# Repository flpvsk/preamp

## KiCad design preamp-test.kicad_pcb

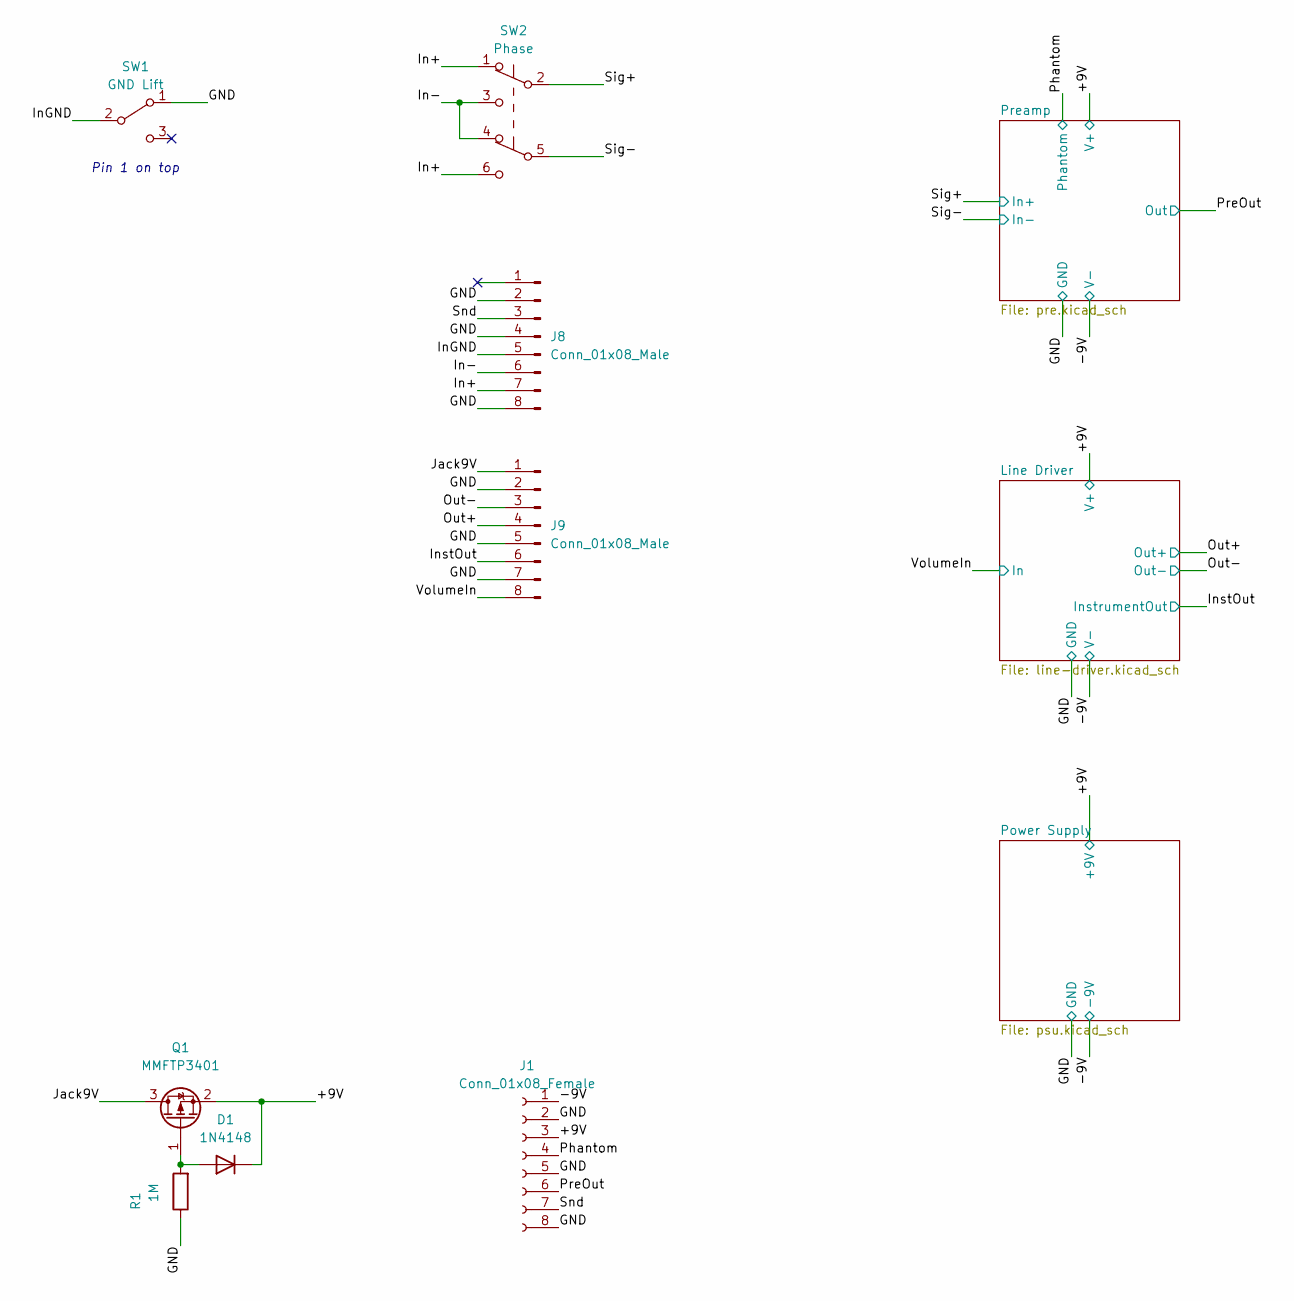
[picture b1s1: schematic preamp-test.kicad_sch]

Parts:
D1: 1N4148; D_SOD-323_HandSoldering
J1: Conn_01x08_Female; PinSocket_1x08_P2.54mm_Vertical
J8, J9: Conn_01x08_Male; Molex_Picoflex_90814-0008_2x04_P1.27mm_Vertical
Q1: MMFTP3401; SOT-23
R1: 1M; R_0603_1608Metric_Pad0.98x0.95mm_HandSolder
SW1: GND Lift; SPDT.LUGS
SW2: Phase; DPDT.LUGS

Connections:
/+9V: D1.1 (K), J1.3, Q1.2 (S); also elsewhere on the board
/-9V: J1.1; also elsewhere on the board
/GND: J1.2, J1.5, J1.8, J8.2, J8.4, J8.8, J9.2, J9.5, J9.7, R1.1, SW1.1 (A); also elsewhere on the board
/In+: J8.7, SW2.1 (A), SW2.6 (C)
/In-: J8.6, SW2.3 (C), SW2.4 (A)
/InGND: J8.5, SW1.2 (B)
/InstOut: J9.6; also elsewhere on the board
/Jack9V: J9.1, Q1.3 (D)
/Out+: J9.4; also elsewhere on the board
/Out-: J9.3; also elsewhere on the board
/Phantom: J1.4; also elsewhere on the board
/PreOut: J1.6; also elsewhere on the board
/Sig+: SW2.2 (B); also elsewhere on the board
/Sig-: SW2.5 (B); also elsewhere on the board
/Snd: J1.7, J8.3
/VolumeIn: J9.8; also elsewhere on the board
unnamed: D1.2 (A), Q1.1 (G), R1.2

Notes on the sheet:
Pin 1 on top

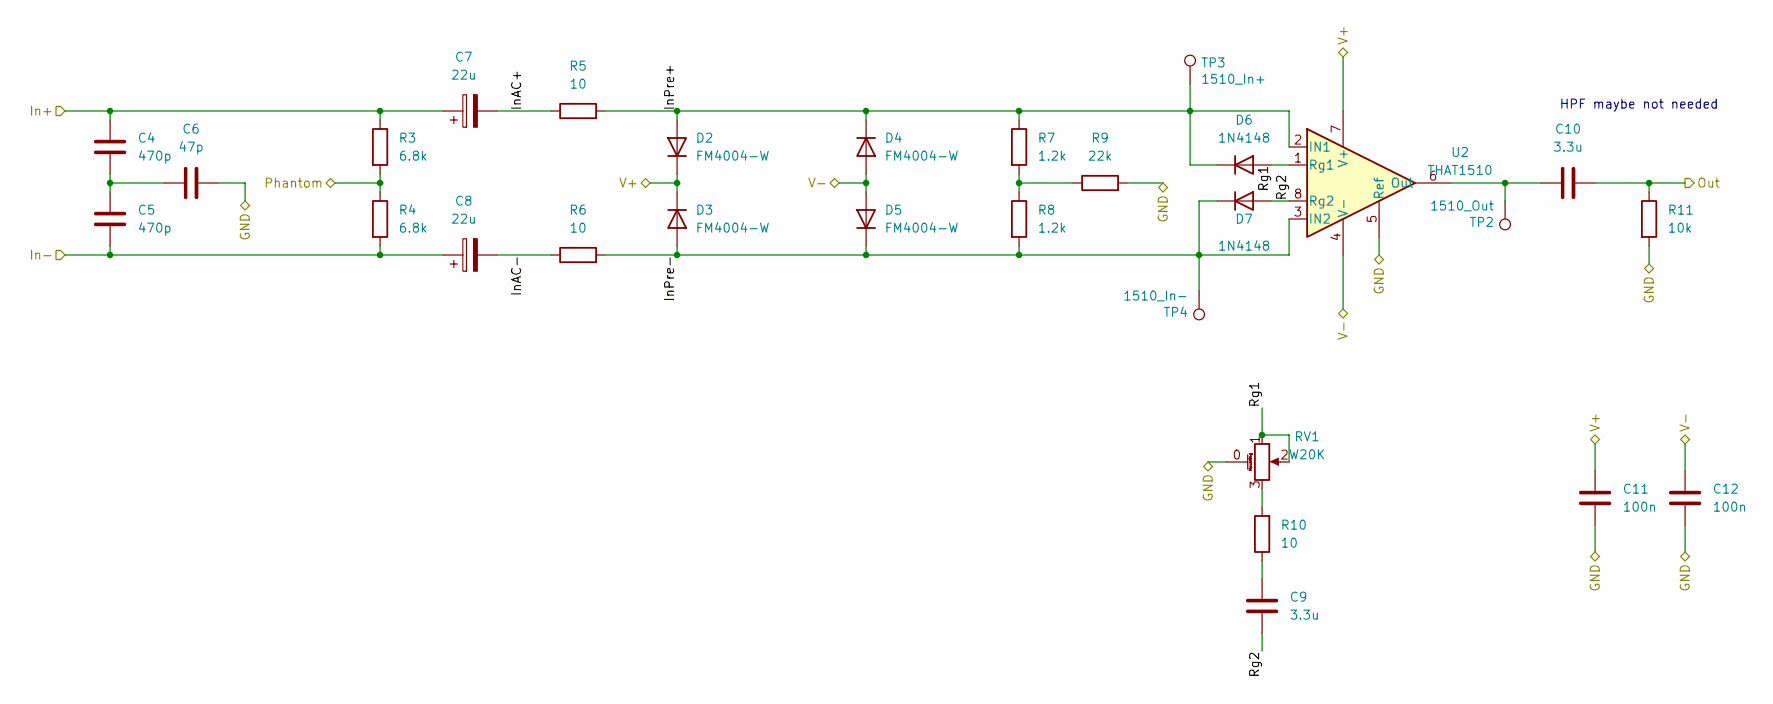
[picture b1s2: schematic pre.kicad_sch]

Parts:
C4, C5: 470p; C_0603_1608Metric_Pad1.08x0.95mm_HandSolder
C6: 47p; C_0603_1608Metric_Pad1.08x0.95mm_HandSolder
C7, C8: 22u; CP_Elec_6.3x5.8
C9, C10: 3.3u; C_1206_3216Metric_Pad1.33x1.80mm_HandSolder
C11, C12: 100n; C_0603_1608Metric_Pad1.08x0.95mm_HandSolder
D2, D3, D4, D5: FM4004-W; D_SMA_Handsoldering
D6, D7: 1N4148; D_SOD-323_HandSoldering
R3, R4: 6.8k; R_0603_1608Metric_Pad0.98x0.95mm_HandSolder
R5, R6, R10: 10; R_0603_1608Metric_Pad0.98x0.95mm_HandSolder
R7, R8: 1.2k; R_0603_1608Metric_Pad0.98x0.95mm_HandSolder
R9: 22k; R_0603_1608Metric_Pad0.98x0.95mm_HandSolder
R11: 10k; R_0603_1608Metric_Pad0.98x0.95mm_HandSolder
RV1: W20K; V3_TRIM_R0904NB10KL-Keepout
TP2: 1510_Out; TestPoint_THTPad_D1.5mm_Drill0.7mm
TP3: 1510_In+; TestPoint_THTPad_D1.5mm_Drill0.7mm
TP4: 1510_In-; TestPoint_THTPad_D1.5mm_Drill0.7mm
U2: THAT1510; SOIC-8_3.9x4.9mm_P1.27mm

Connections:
/+9V: C11.2, D2.1 (K), D3.1 (K), U2.7 (V+); also elsewhere on the board
/-9V: C12.2, D4.2 (A), D5.2 (A), U2.4 (V-); also elsewhere on the board
/GND: C6.2, C11.1, C12.1, R9.2, R11.2, RV1.0 (ShieldPin), U2.5 (Ref); also elsewhere on the board
/Phantom: R3.2, R4.1; also elsewhere on the board
/PreOut: C10.2, R11.1; also elsewhere on the board
/Preamp/InAC+: C7.2, R5.1
/Preamp/InAC-: C8.2, R6.1
/Preamp/InPre+: D2.2 (A), D4.1 (K), D6.1 (K), R5.2, R7.1, TP3.1, U2.2 (IN1)
/Preamp/InPre-: D3.2 (A), D5.1 (K), D7.1 (K), R6.2, R8.2, TP4.1, U2.3 (IN2)
/Preamp/Rg1: D6.2 (A), RV1.1, RV1.2, U2.1 (Rg1)
/Preamp/Rg2: C9.2, D7.2 (A), U2.8 (Rg2)
/Sig+: C4.1, C7.1, R3.1; also elsewhere on the board
/Sig-: C5.2, C8.1, R4.2; also elsewhere on the board
unnamed: C4.2, C5.1, C6.1
unnamed: C9.1, R10.1
unnamed: C10.1, TP2.1, U2.6 (Out)
unnamed: R7.2, R8.1, R9.1
unnamed: R10.2, RV1.3

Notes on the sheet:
HPF maybe not needed

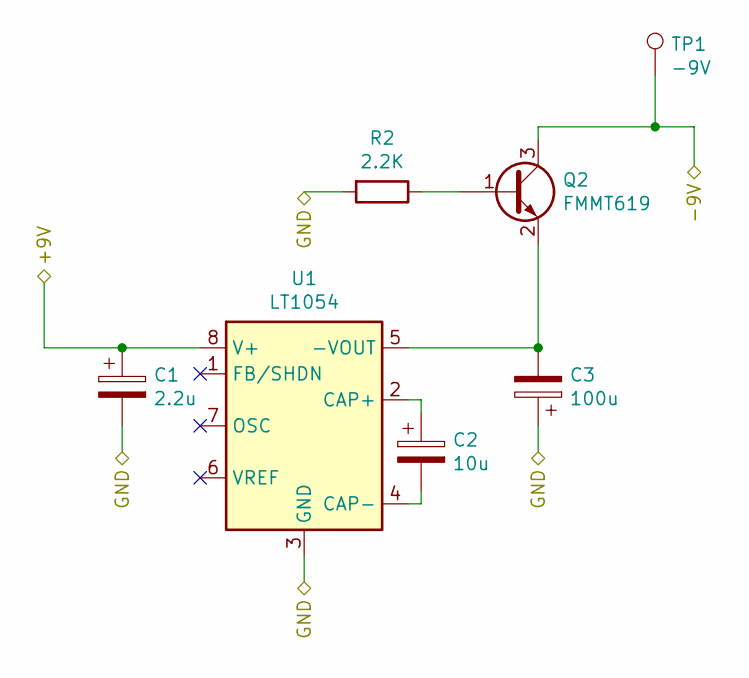
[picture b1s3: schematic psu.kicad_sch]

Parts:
C1: 2.2u; CP_Elec_4x5.4
C2: 10u; CP_EIA-6032-28_Kemet-C_Pad2.25x2.35mm_HandSolder
C3: 100u; CP_EIA-6032-28_Kemet-C_Pad2.25x2.35mm_HandSolder
Q2: FMMT619; SOT-23_Handsoldering
R2: 2.2K; R_0603_1608Metric_Pad0.98x0.95mm_HandSolder
TP1: -9V; TestPoint_THTPad_D1.5mm_Drill0.7mm
U1: LT1054; SOIC-8_3.9x4.9mm_P1.27mm

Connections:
/+9V: C1.1, U1.8 (V+); also elsewhere on the board
/-9V: Q2.3 (C), TP1.1; also elsewhere on the board
/GND: C1.2, C3.1, R2.2, U1.3 (GND); also elsewhere on the board
unnamed: C2.1, U1.2 (CAP+)
unnamed: C2.2, U1.4 (CAP-)
unnamed: C3.2, Q2.2 (E), U1.5 (-VOUT)
unnamed: Q2.1 (B), R2.1

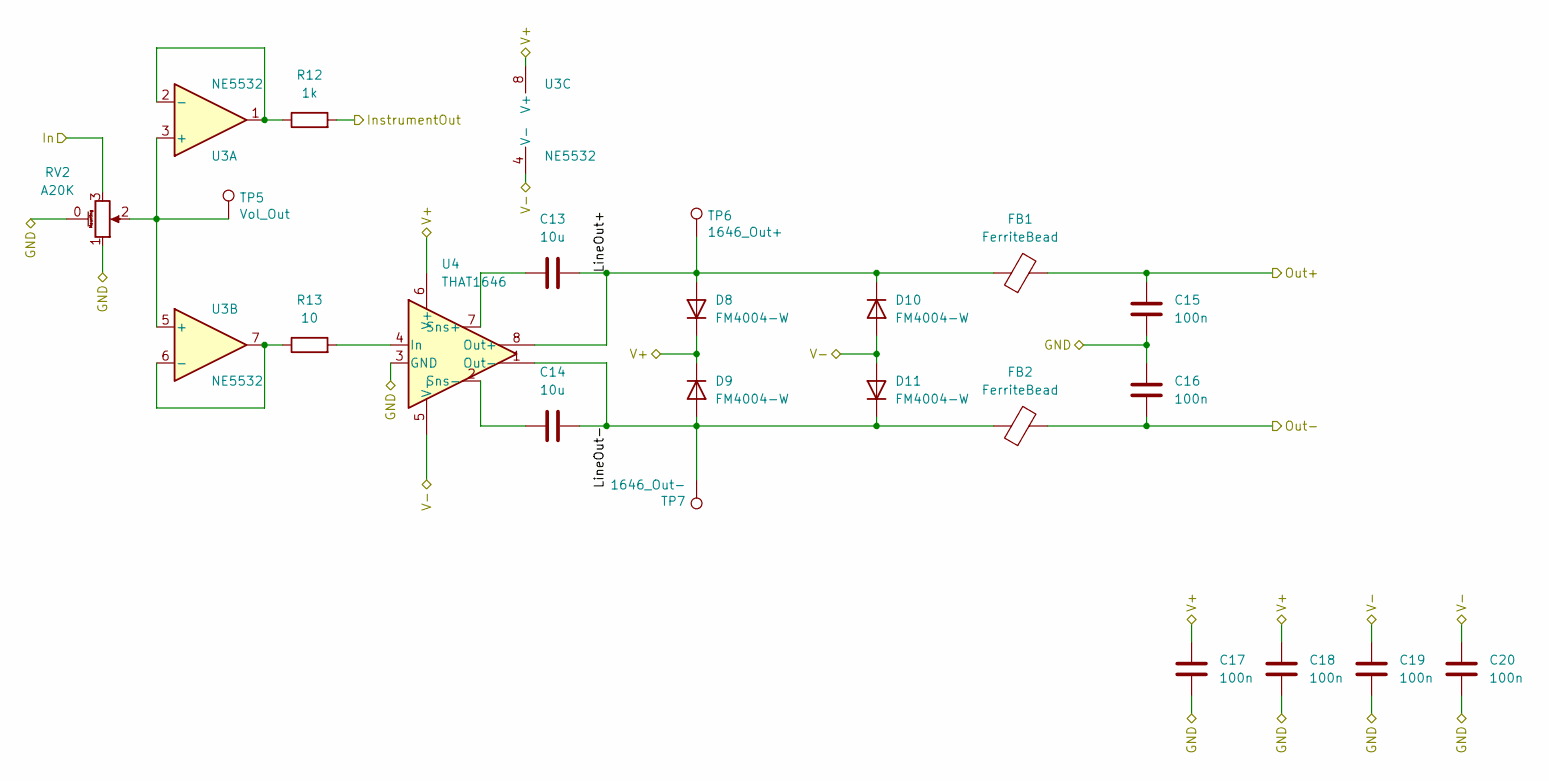
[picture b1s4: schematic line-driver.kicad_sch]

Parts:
C13, C14: 10u; C_1206_3216Metric_Pad1.33x1.80mm_HandSolder
C15, C16, C17, C18, C19, C20: 100n; C_0603_1608Metric_Pad1.08x0.95mm_HandSolder
D8, D9, D10, D11: FM4004-W; D_SMA_Handsoldering
FB1, FB2: FerriteBead; R_0603_1608Metric_Pad0.98x0.95mm_HandSolder
R12: 1k; R_0603_1608Metric_Pad0.98x0.95mm_HandSolder
R13: 10; R_0603_1608Metric_Pad0.98x0.95mm_HandSolder
RV2: A20K; V3_TRIM_R0904NB10KL-Keepout
TP5: Vol_Out; TestPoint_THTPad_D1.5mm_Drill0.7mm
TP6: 1646_Out+; TestPoint_THTPad_D1.5mm_Drill0.7mm
TP7: 1646_Out-; TestPoint_THTPad_D1.5mm_Drill0.7mm
U3: NE5532; SOIC-8_3.9x4.9mm_P1.27mm
U4: THAT1646; SOIC-8_3.9x4.9mm_P1.27mm

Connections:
/+9V: C17.2, C18.2, D8.1 (K), D9.1 (K), U3.8 (V+), U4.6 (V+); also elsewhere on the board
/-9V: C19.2, C20.2, D10.2 (A), D11.2 (A), U3.4 (V-), U4.5 (V-); also elsewhere on the board
/GND: C15.1, C16.2, C17.1, C18.1, C19.1, C20.1, RV2.0 (ShieldPin), RV2.1, U4.3 (GND); also elsewhere on the board
/InstOut: R12.2; also elsewhere on the board
/Line Driver/LineOut+: C13.2, D8.2 (A), D10.1 (K), FB1.1, TP6.1, U4.8 (Out+)
/Line Driver/LineOut-: C14.2, D9.2 (A), D11.1 (K), FB2.1, TP7.1, U4.1 (Out-)
/Out+: C15.2, FB1.2; also elsewhere on the board
/Out-: C16.1, FB2.2; also elsewhere on the board
/VolumeIn: RV2.3; also elsewhere on the board
unnamed: C13.1, U4.7 (Sns+)
unnamed: C14.1, U4.2 (Sns-)
unnamed: R12.1, U3.1, U3.2 (-)
unnamed: R13.1, U3.6 (-), U3.7
unnamed: R13.2, U4.4 (In)
unnamed: RV2.2, TP5.1, U3.3 (+), U3.5 (+)

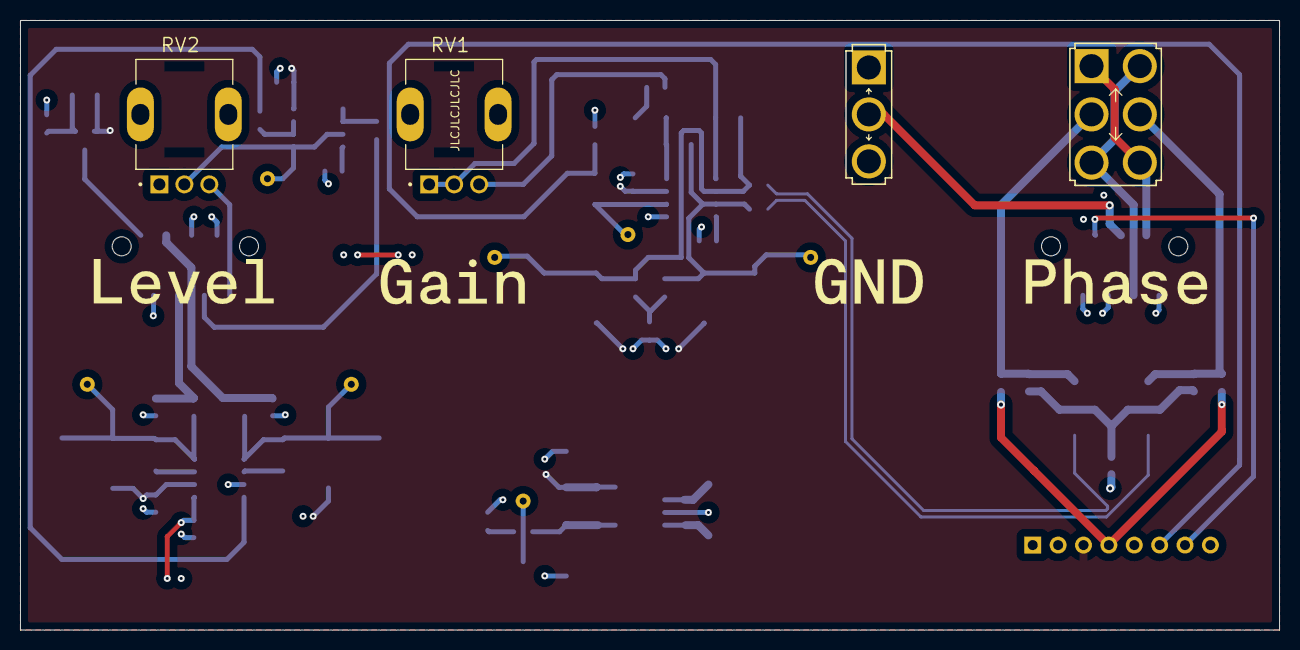
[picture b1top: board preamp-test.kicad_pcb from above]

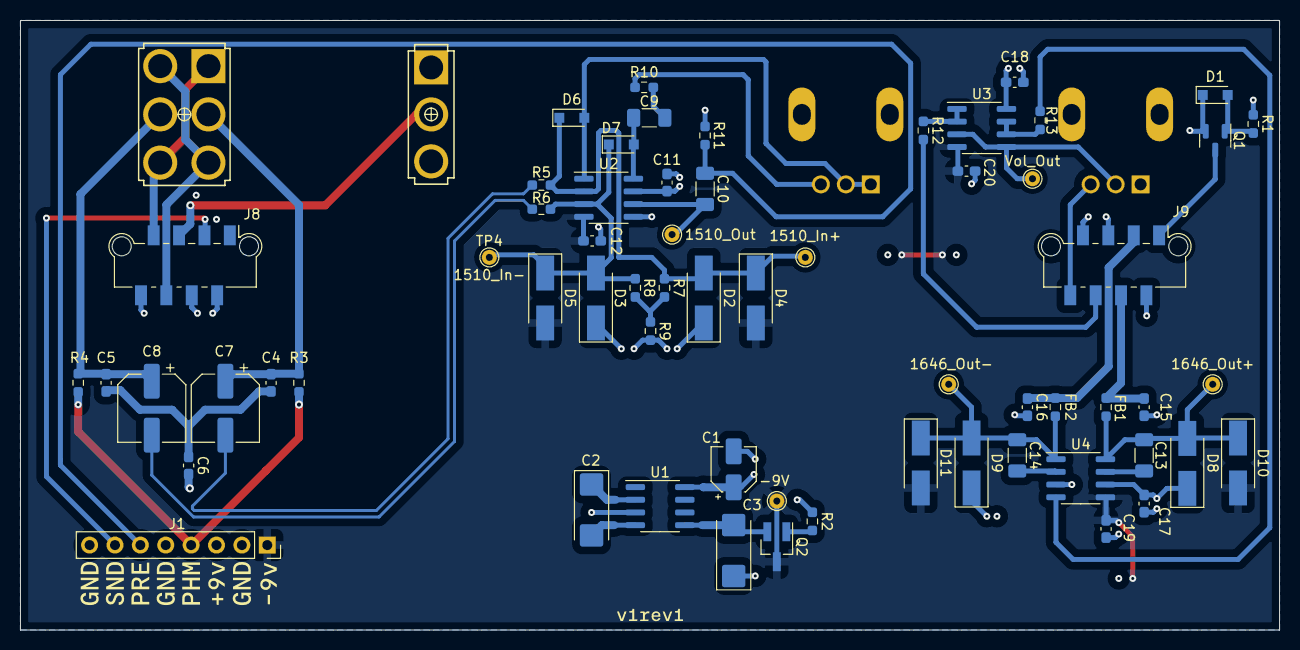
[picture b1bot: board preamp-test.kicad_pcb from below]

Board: 4 copper layers, 126.0 x 61.0 mm, 80 parts (71 on the bottom side), 40 nets.

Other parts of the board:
Ref**: Val**; 1590XX
kibuzzard-66CA6E97: G***; kibuzzard-66CA6E97
kibuzzard-66CA6ECA: G***; kibuzzard-66CA6ECA
kibuzzard-66CA6F29: G***; kibuzzard-66CA6F29
kibuzzard-66CA6F40: G***; kibuzzard-66CA6F40
kibuzzard-66CB7A1F: G***; kibuzzard-66CB7A1F
kibuzzard-66CB7A30, kibuzzard-66CB7A30#2, kibuzzard-66CB7A30#3: G***; kibuzzard-66CB7A30
kibuzzard-66CB7A55: G***; kibuzzard-66CB7A55
kibuzzard-66CB7AA0: G***; kibuzzard-66CB7AA0
kibuzzard-66CB7AA6: G***; kibuzzard-66CB7AA6
kibuzzard-66CB7AAB: G***; kibuzzard-66CB7AAB
kibuzzard-66CB7C93: G***; kibuzzard-66CB7C93

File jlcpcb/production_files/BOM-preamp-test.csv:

Comment,Designator,Footprint,LCSC
Conn_01x08_Female,J1,PinSocket_1x08_P2.54mm_Vertical,
GND Lift,SW1,SPDT.LUGS,
A20K,RV2,V3_TRIM_R0904NB10KL-Keepout,
W20K,RV1,V3_TRIM_R0904NB10KL-Keepout,
Phase,SW2,DPDT.LUGS,
2.2K,R2,R_0603_1608Metric_Pad0.98x0.95mm_HandSolder,
1.2k,R7,R_0603_1608Metric_Pad0.98x0.95mm_HandSolder,
100n,C17,C_0603_1608Metric_Pad1.08x0.95mm_HandSolder,
10,R5,R_0603_1608Metric_Pad0.98x0.95mm_HandSolder,
MMFTP3401,Q1,SOT-23,
Conn_01x08_Male,J8,Molex_Picoflex_90814-0008_2x04_P1.27mm_Vertical,
1N4148,D1,D_SOD-323_HandSoldering,
1510_In+,TP3,TestPoint_THTPad_D1.5mm_Drill0.7mm,
1k,R12,R_0603_1608Metric_Pad0.98x0.95mm_HandSolder,
FM4004-W,D3,D_SMA_Handsoldering,
10,R6,R_0603_1608Metric_Pad0.98x0.95mm_HandSolder,
47p,C6,C_0603_1608Metric_Pad1.08x0.95mm_HandSolder,
22k,R9,R_0603_1608Metric_Pad0.98x0.95mm_HandSolder,
-9V,TP1,TestPoint_THTPad_D1.5mm_Drill0.7mm,
100n,C20,C_0603_1608Metric_Pad1.08x0.95mm_HandSolder,
1510_In-,TP4,TestPoint_THTPad_D1.5mm_Drill0.7mm,
FM4004-W,D10,D_SMA_Handsoldering,
Conn_01x08_Male,J9,Molex_Picoflex_90814-0008_2x04_P1.27mm_Vertical,
THAT1510,U2,SOIC-8_3.9x4.9mm_P1.27mm,
FM4004-W,D5,D_SMA_Handsoldering,
LT1054,U1,SOIC-8_3.9x4.9mm_P1.27mm,
1646_Out-,TP7,TestPoint_THTPad_D1.5mm_Drill0.7mm,
FMMT619,Q2,SOT-23_Handsoldering,
FM4004-W,D8,D_SMA_Handsoldering,
10u,C14,C_1206_3216Metric_Pad1.33x1.80mm_HandSolder,
1N4148,D6,D_SOD-323_HandSoldering,
1510_Out,TP2,TestPoint_THTPad_D1.5mm_Drill0.7mm,
3.3u,C9,C_1206_3216Metric_Pad1.33x1.80mm_HandSolder,
100n,C16,C_0603_1608Metric_Pad1.08x0.95mm_HandSolder,
2.2u,C1,CP_Elec_4x5.4,
1.2k,R8,R_0603_1608Metric_Pad0.98x0.95mm_HandSolder,
10u,C13,C_1206_3216Metric_Pad1.33x1.80mm_HandSolder,
1646_Out+,TP6,TestPoint_THTPad_D1.5mm_Drill0.7mm,
22u,C8,CP_Elec_6.3x5.8,
22u,C7,CP_Elec_6.3x5.8,
100n,C19,C_0603_1608Metric_Pad1.08x0.95mm_HandSolder,
10u,C2,CP_EIA-6032-28_Kemet-C_Pad2.25x2.35mm_HandSolder,
FM4004-W,D9,D_SMA_Handsoldering,
FerriteBead,FB2,R_0603_1608Metric_Pad0.98x0.95mm_HandSolder,
6.8k,R4,R_0603_1608Metric_Pad0.98x0.95mm_HandSolder,
100n,C12,C_0603_1608Metric_Pad1.08x0.95mm_HandSolder,
FM4004-W,D2,D_SMA_Handsoldering,
100n,C11,C_0603_1608Metric_Pad1.08x0.95mm_HandSolder,
10,R10,R_0603_1608Metric_Pad0.98x0.95mm_HandSolder,
100n,C15,C_0603_1608Metric_Pad1.08x0.95mm_HandSolder,
470p,C4,C_0603_1608Metric_Pad1.08x0.95mm_HandSolder,
10k,R11,R_0603_1608Metric_Pad0.98x0.95mm_HandSolder,
THAT1646,U4,SOIC-8_3.9x4.9mm_P1.27mm,
100n,C18,C_0603_1608Metric_Pad1.08x0.95mm_HandSolder,
1N4148,D7,D_SOD-323_HandSoldering,
6.8k,R3,R_0603_1608Metric_Pad0.98x0.95mm_HandSolder,
NE5532,U3,SOIC-8_3.9x4.9mm_P1.27mm,
10,R13,R_0603_1608Metric_Pad0.98x0.95mm_HandSolder,
FerriteBead,FB1,R_0603_1608Metric_Pad0.98x0.95mm_HandSolder,
FM4004-W,D4,D_SMA_Handsoldering,
Vol_Out,TP5,TestPoint_THTPad_D1.5mm_Drill0.7mm,
100u,C3,CP_EIA-6032-28_Kemet-C_Pad2.25x2.35mm_HandSolder,
FM4004-W,D11,D_SMA_Handsoldering,
470p,C5,C_0603_1608Metric_Pad1.08x0.95mm_HandSolder,
1M,R1,R_0603_1608Metric_Pad0.98x0.95mm_HandSolder,
3.3u,C10,C_1206_3216Metric_Pad1.33x1.80mm_HandSolder,

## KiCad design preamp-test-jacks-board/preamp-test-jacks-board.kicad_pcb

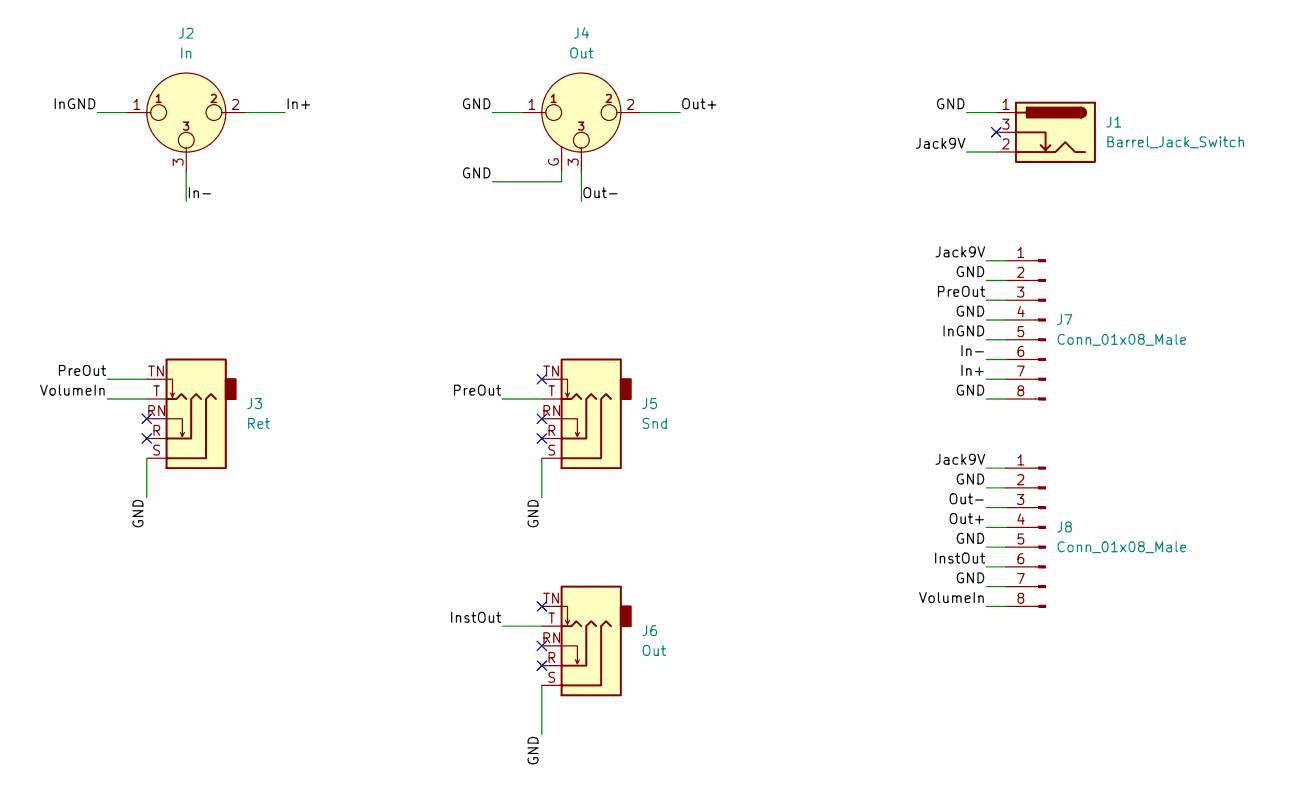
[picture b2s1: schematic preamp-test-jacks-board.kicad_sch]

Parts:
J1: Barrel_Jack_Switch; BarrelJack_GCT_DCJ200-10-A_Horizontal
J2: In; Jack_XLR_Neutrik_NC3FAH-0_Horizontal
J3: Ret; tayda-6mm35-jack-pcb-compact
J4: Out; Jack_XLR_Neutrik_NC3MAH-0_Horizontal
J5: Snd; tayda-6mm35-jack-pcb-compact
J6: Out; tayda-6mm35-jack-pcb-compact
J7, J8: Conn_01x08_Male; Molex_Picoflex_90814-0008_2x04_P1.27mm_Vertical

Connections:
/GND: J1.1, J3.S, J4.1, J4.G, J5.S, J6.S, J7.2, J7.4, J7.8, J8.2, J8.5, J8.7
/In+: J2.2, J7.7
/In-: J2.3, J7.6
/InGND: J2.1, J7.5
/InstOut: J6.T, J8.6
/Jack9V: J1.2, J7.1, J8.1
/Out+: J4.2, J8.4
/Out-: J4.3, J8.3
/PreOut: J3.TN, J5.T, J7.3
/VolumeIn: J3.T, J8.8

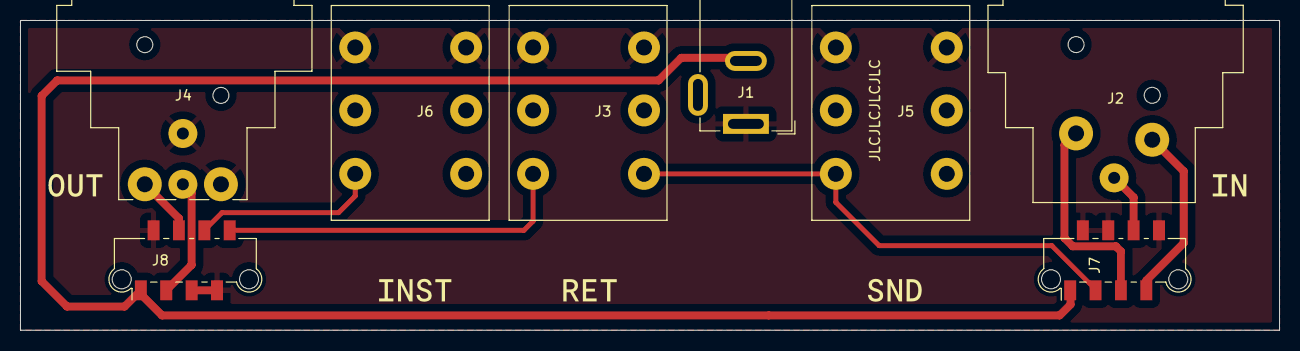
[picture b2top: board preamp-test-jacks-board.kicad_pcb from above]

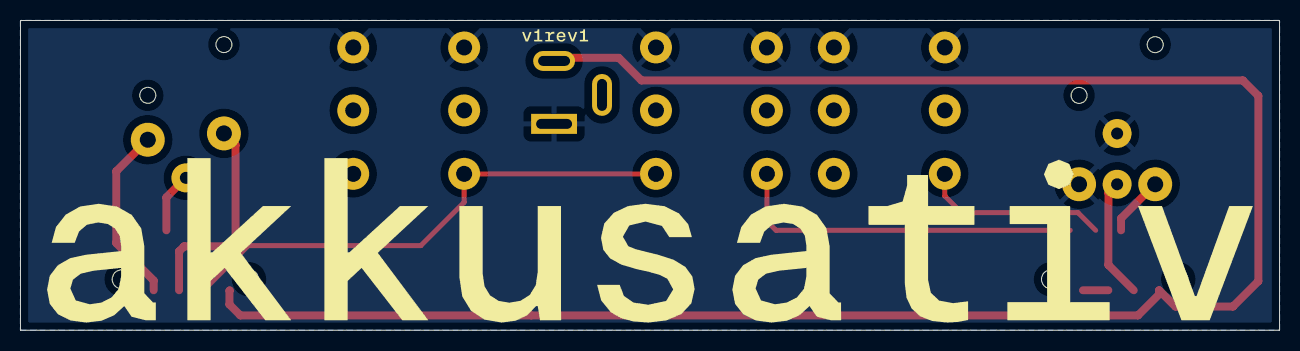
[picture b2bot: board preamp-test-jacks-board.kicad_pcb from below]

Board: 2 copper layers, 126.0 x 31.0 mm, 16 parts (2 on the bottom side), 10 nets.

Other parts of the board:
Ref**: Val**; 1590XX
kibuzzard-66CA4BD9: G***; kibuzzard-66CA4BD9
kibuzzard-66CA4C2E: G***; kibuzzard-66CA4C2E
kibuzzard-66CA4C4C: G***; kibuzzard-66CA4C4C
kibuzzard-66CA4C11: G***; kibuzzard-66CA4C11
kibuzzard-66CA4D8D: G***; kibuzzard-66CA4D8D
kibuzzard-66CB7BC6: G***; kibuzzard-66CB7BC6
kibuzzard-66CB7C17: G***; kibuzzard-66CB7C17

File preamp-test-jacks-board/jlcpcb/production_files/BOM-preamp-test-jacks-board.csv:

Comment,Designator,Footprint,LCSC
Conn_01x08_Male,J8,Molex_Picoflex_90814-0008_2x04_P1.27mm_Vertical,
Out,J4,Jack_XLR_Neutrik_NC3MAH-0_Horizontal,
Barrel_Jack_Switch,J1,BarrelJack_GCT_DCJ200-10-A_Horizontal,
Conn_01x08_Male,J7,Molex_Picoflex_90814-0008_2x04_P1.27mm_Vertical,
Out,J6,tayda-6mm35-jack-pcb-compact,
Snd,J5,tayda-6mm35-jack-pcb-compact,
In,J2,Jack_XLR_Neutrik_NC3FAH-0_Horizontal,
Ret,J3,tayda-6mm35-jack-pcb-compact,

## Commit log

2024-08-07 Init
2024-08-08 Start layout
2024-08-24 Layout draft done
2024-08-25 More ext options
2024-08-25 Ordered at JLC
